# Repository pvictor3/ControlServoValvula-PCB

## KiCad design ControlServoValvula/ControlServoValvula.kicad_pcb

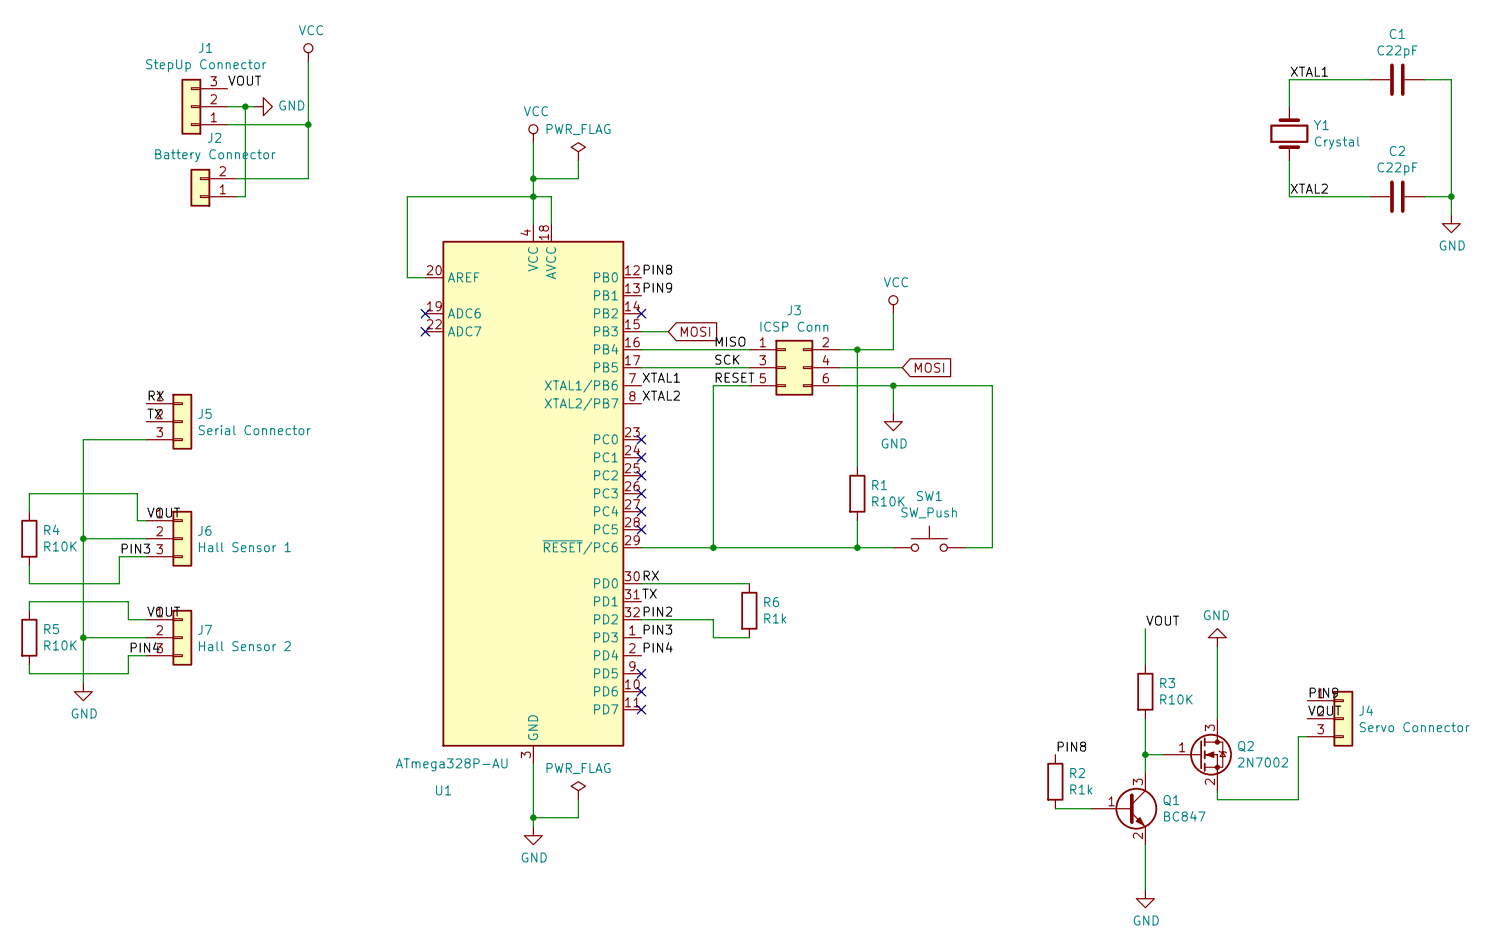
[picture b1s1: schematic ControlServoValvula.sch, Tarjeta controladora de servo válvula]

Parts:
C1, C2: C22pF; C_0603_1608Metric
J1: StepUp Connector; PinHeader_1x03_P2.54mm_Vertical
J2: Battery Connector; TerminalBlock_bornier-2_P5.08mm
J3: ICSP Conn; PinHeader_2x03_P2.54mm_Vertical
J4: Servo Connector; PinHeader_1x03_P2.54mm_Horizontal
J5: Serial Connector; JST_EH_S03B-EH_1x03_P2.50mm_Horizontal
J6: Hall Sensor 1; JST_EH_S03B-EH_1x03_P2.50mm_Horizontal
J7: Hall Sensor 2; JST_EH_S03B-EH_1x03_P2.50mm_Horizontal
Q1: BC847; SOT-23
Q2: 2N7002; SOT-23
R1, R3, R4, R5: R10K; R_0603_1608Metric
R2, R6: R1k; R_0603_1608Metric
SW1: SW_Push; SW_SPST_EVPBF
U1: ATmega328P-AU; TQFP-32_7x7mm_P0.8mm
Y1: Crystal; Crystal_HC49-4H_Vertical

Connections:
/MISO: J3.1, U1.16 (PB4)
/PIN2: R6.2, U1.32 (PD2)
/PIN3: J6.3, R4.2, U1.1 (PD3)
/PIN4: J7.3, R5.2, U1.2 (PD4)
/PIN8: R2.1, U1.12 (PB0)
/PIN9: J4.1, U1.13 (PB1)
/RESET: J3.5, R1.2, SW1.1, U1.29 (~RESET~/PC6)
/RX: J5.1, R6.1, U1.30 (PD0)
/SCK: J3.3, U1.17 (PB5)
/TX: J5.2, U1.31 (PD1)
/VOUT: J1.3, J4.2, J6.1, J7.1, R3.1, R4.1, R5.1
/XTAL1: C1.2, U1.7 (XTAL1/PB6), Y1.2
/XTAL2: C2.2, U1.8 (XTAL2/PB7), Y1.1
GND: C1.1, C2.1, J1.2, J2.1, J3.6, J5.3, J6.2, J7.2, Q1.2 (E), Q2.3 (D), SW1.2, U1.3 (GND), U1.5 (GND), U1.21 (GND)
MOSI: J3.4, U1.15 (PB3)
unnamed: J4.3, Q2.2 (S)
unnamed: Q1.1 (B), R2.2
unnamed: Q1.3 (C), Q2.1 (G), R3.2
VCC: J1.1, J2.2, J3.2, R1.1, U1.4 (VCC), U1.6 (VCC), U1.18 (AVCC), U1.20 (AREF)

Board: 2 copper layers, 20 parts (0 on the bottom side), 19 nets, no tracks yet.

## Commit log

2019-03-02 Creacion esquematico y pcb en kicad
